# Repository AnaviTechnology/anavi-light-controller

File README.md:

# ANAVI Light Controller

ANAVI Light Controller is an open source hardware board for controlling 12V RGB LED strip powered by free and open source software. It features:

* Slot for RGB LED strip
* 12V input for the RGB LED strip
* Slots for up to 3 plug and play I2C sensors for temperature, barometric pressure, humidity and light
* UART (Universal asynchronous receiver/transmitter) pins for debugging

Open source software for ANAVI Light Controller written as an Arduino sketch is also available at [GitHub](https://github.com/AnaviTechnology/anavi-light-controller-sw).

# License

The project is released under the [Creative Commons Attribution-ShareAlike 4.0 International (CC BY-SA 4.0)](https://creativecommons.org/licenses/by-sa/4.0/).

Note: This is a human-readable summary of (and not a substitute for) the [license](https://creativecommons.org/licenses/by-sa/4.0/legalcode).

You are free to:

Share — copy and redistribute the material in any medium or format Adapt — remix, transform, and build upon the material for any purpose, even commercially. The licensor cannot revoke these freedoms as long as you follow the license terms. Under the following terms:

Attribution — You must give appropriate credit, provide a link to the license, and indicate if changes were made. You may do so in any reasonable manner, but not in any way that suggests the licensor endorses you or your use. ShareAlike — If you remix, transform, or build upon the material, you must distribute your contributions under the same license as the original. No additional restrictions — You may not apply legal terms or technological measures that legally restrict others from doing anything the license permits. Notices:

You do not have to comply with the license for elements of the material in the public domain or where your use is permitted by an applicable exception or limitation. No warranties are given. The license may not give you all of the permissions necessary for your intended use. For example, other rights such as publicity, privacy, or moral rights may limit how you use the material.

You will have to provide a link to the original creator of the project http://www.anavi.technology on any documentation or website.

Credit can be attributed through a link to the creator website: http://www.anavi.technology

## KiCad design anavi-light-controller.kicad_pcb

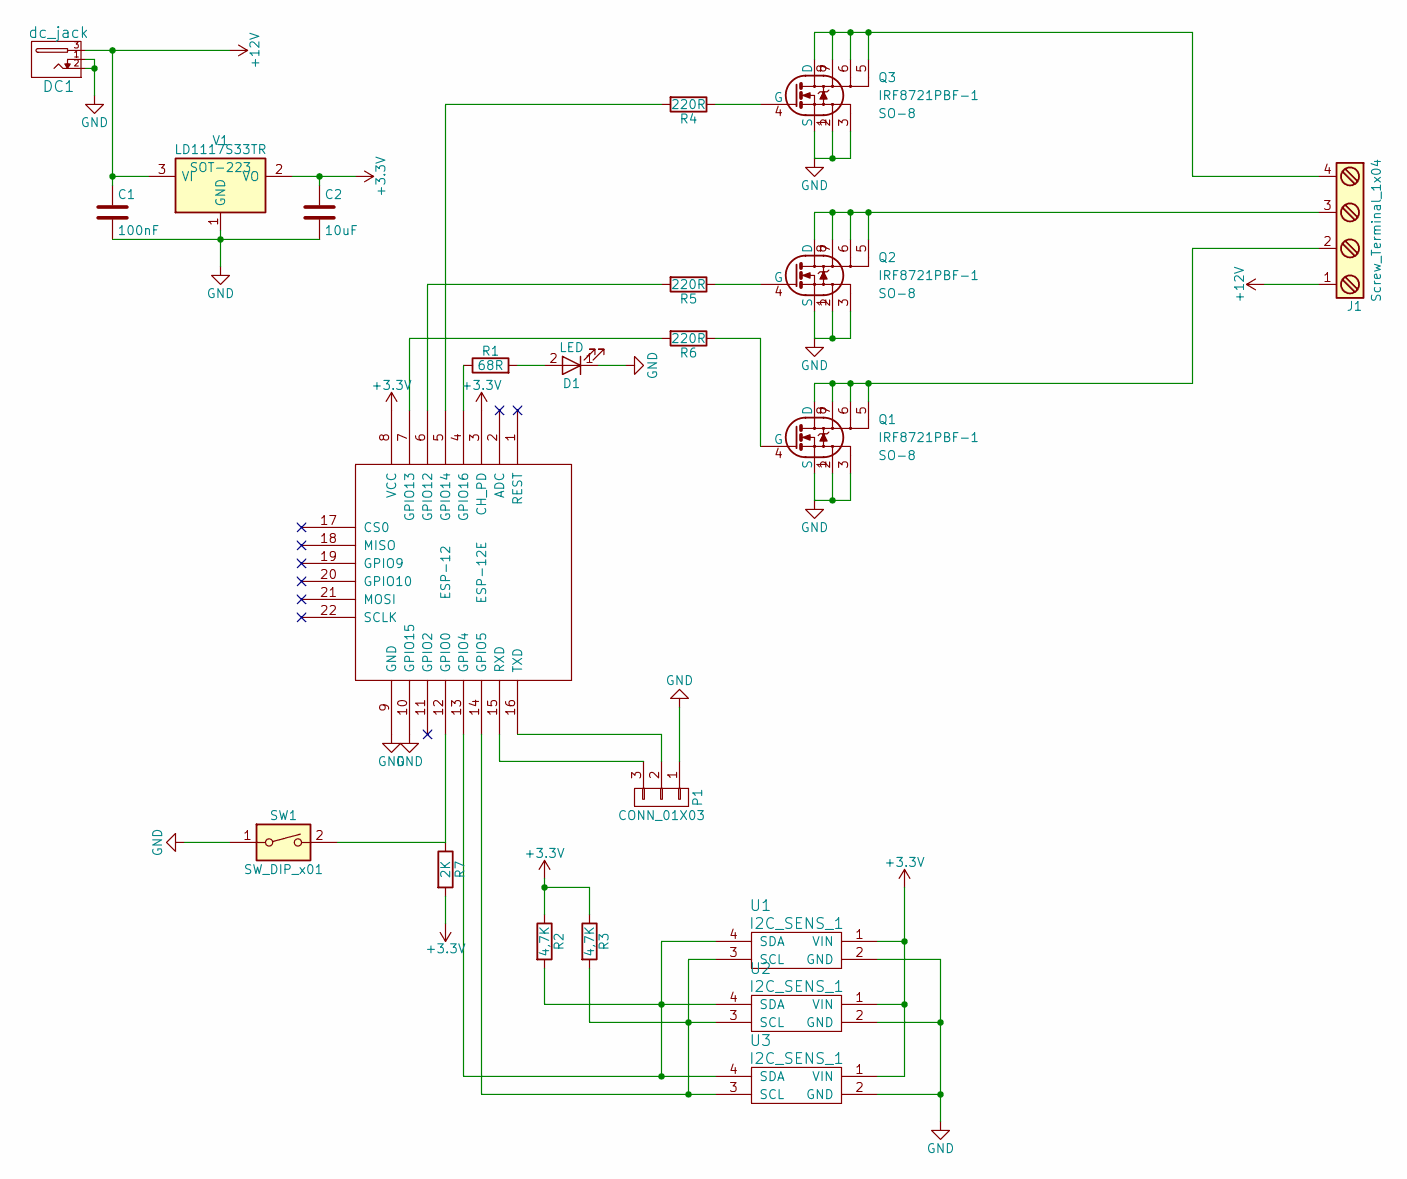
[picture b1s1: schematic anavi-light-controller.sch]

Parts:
C1: 100nF; C_0603_HandSoldering
C2: 10uF; C_0805_HandSoldering
D1: LED; LED_1206
DC1: dc_jack; dc_socket
ESP-12: ESP-12E; ESP-12E_SMD
J1: Screw_Terminal_1x04; TerminalBlock_Pheonix_MKDS1.5-4pol
P1: CONN_01X03; Pin_Header_Straight_1x03
Q1, Q2, Q3: IRF8721PBF-1; SO-8
R1: 68R; R_0603_HandSoldering
R2, R3: 4,7K; R_0603_HandSoldering
R4, R5, R6: 220R; R_0603_HandSoldering
R7: 2K; C_0603_HandSoldering
SW1: SW_DIP_x01; SW_PUSH_6mm_h4.3mm
U1, U2, U3: I2C_SENS_1; Pin_Header_Straight_1x04
V1: LD1117S33TR; SOT-223

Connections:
+3V3: C2.1, ESP-12.3 (CH_PD), ESP-12.8 (VCC), R2.1, R3.1, R7.2, U1.1 (VIN), U2.1 (VIN), U3.1 (VIN), V1.2 (VO)
+12V: C1.1, DC1.3, J1.1, V1.3 (VI)
GND: C1.2, C2.2, D1.1 (K), DC1.1, DC1.2, ESP-12.9 (GND), ESP-12.10 (GPIO15), P1.1, Q1.1 (S), Q1.2, Q1.3, Q2.1 (S), Q2.2, Q2.3, Q3.1 (S), Q3.2, Q3.3, SW1.1, U1.2 (GND), U2.2 (GND), U3.2 (GND), V1.1 (GND)
unnamed: D1.2 (A), R1.2
unnamed: ESP-12.4 (GPIO16), R1.1
unnamed: ESP-12.5 (GPIO14), R4.2
unnamed: ESP-12.6 (GPIO12), R5.2
unnamed: ESP-12.7 (GPIO13), R6.2
unnamed: ESP-12.12 (GPIO0), R7.1, SW1.2
unnamed: ESP-12.13 (GPIO4), R2.2, U1.4 (SDA), U2.4 (SDA), U3.4 (SDA)
unnamed: ESP-12.14 (GPIO5), R3.2, U1.3 (SCL), U2.3 (SCL), U3.3 (SCL)
unnamed: ESP-12.15 (RXD), P1.3
unnamed: ESP-12.16 (TXD), P1.2
unnamed: J1.2, Q1.5, Q1.6, Q1.7, Q1.8 (D)
unnamed: J1.3, Q2.5, Q2.6, Q2.7, Q2.8 (D)
unnamed: J1.4, Q3.5, Q3.6, Q3.7, Q3.8 (D)
unnamed: Q1.4 (G), R6.1
unnamed: Q2.4 (G), R5.1
unnamed: Q3.4 (G), R4.1

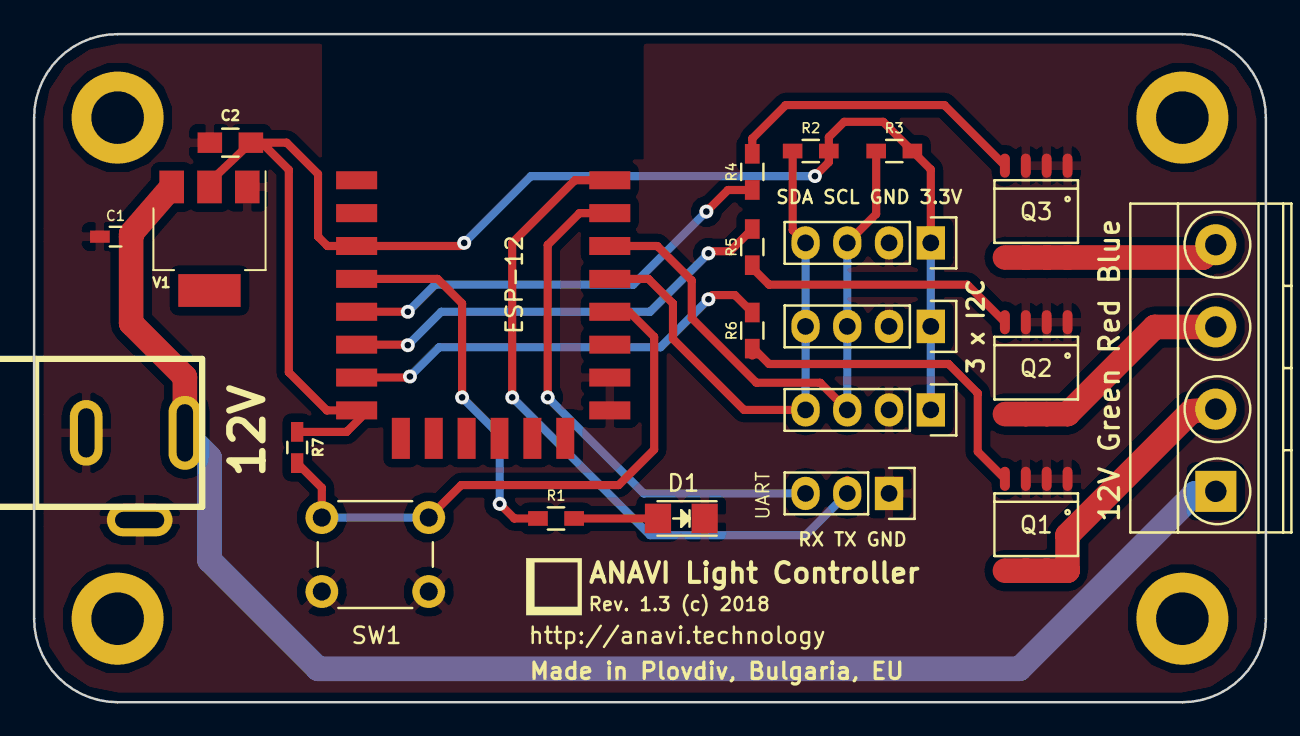
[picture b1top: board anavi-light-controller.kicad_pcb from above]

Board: 2 copper layers, 74.9 x 40.6 mm, 22 parts (0 on the bottom side), 19 nets.

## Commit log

2017-08-10 anavi-light-controller: Initial version
2017-08-10 anavi-light-controller: Add labels
2017-08-10 anavi-light-controller.kicad_pcb: Rotate I2C
2017-08-10 anavi-light-controller.kicad_pcb: Increase tracks
    Increace 12V tracks and change the positions of
    the capacitors.
2017-08-10 anavi-light-controller.kicad_pcb: no vias
2017-08-10 anavi-light-controller.kicad_pcb: reduce
    Reduce width of the PCB and change the mounting holes.
2017-09-12 Change LDO voltage regulator
    Use LD1117S33TR as LDO voltage regulator to drop
    from 12V to 3.3V and to power the ESP8266 module.
2017-09-12 Enable ESP-12; Fix the button and LED
    Enable ESP-12 by connecting GPIO5 to GND and CH_PD
    to 3.3V. Add 2K resistor to GPIO0 to fix the button
    and move the alarm LED on the other side.
2017-09-13 kicad_pcb: Adjust positions of components
    Adjust the positions of the red LED and the button.
2017-09-13 kicad_pcb: Increase font of the product name
2018-03-31 rev1.2: Use SMD footprint for ESP-12E
    Use SMD footprint for ESP-12E to simplify the
    assembly, updated product version and routing.
2018-04-04 anavi-light-controller.kicad_pcb: Keepout zones
    Add keepout zones below the ESP-12 antenna.
2018-04-15 README.md: CC BY-SA 4.0
    Switch license to CC BY-SA 4.0 to comply with
    the requirements for open source hardware.
2018-04-15 README.md: Add link to software
    Add details and link to the open source software.
2018-04-26 anavi-light-controller.kicad_pcb: Fix ESP12 wiring
    Fix the wiring of ESP12 as two pins must be
    connected to 3.3V in order to work properly.
2018-05-07 ESP-12E_SMD.kicad_mod: Remove silkscreen from pads
    Remove white silkscreen line from pads.
2018-05-07 anavi-light-controller.kicad_pcb: Rotate ESP-12E
    Rotate ESP8266 model ESP-12E to 90 degrees to
    improve the signal strenght of the WiFi antenna
    and increase the revision to 1.3.
    Huge thanks for the suggested improvements to Jon
    Raymond (twitter: @Jon_Raymond_) and John Lee
    (twitter: @EspressifSystem).
2018-05-08 anavi-light-controller-brd.svg: Assembly
    Add image with assembly instructions.
2018-05-08 anavi-light-controller.kicad_pcb: Improve routing
    Improve the 3.3V wiring.
2018-10-30 Fix markdown link
2018-11-03 README.md: Fix typo in page title
    s/Contoroller/Controller/

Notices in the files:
anavi-light-controller.kicad_pcb:
Rev. 1.3 (c) 2018
